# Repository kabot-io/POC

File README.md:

# Kabot - lowering entry barrier to ROS2

The Kabot robot is a hardware and software solution that lowers the entry barrier to Robot Operating System 2 (ROS2) and provides an expandable platform for makers, students and educators. One of the main obstacles in the adoption of ROS2 by beginners is the high knowledge barrier needed to setup and start tinkering - Kabot mission is to bring batteries included in a box. Think of using Arduino instead of setting up whole toolchain and build system.

The robot is a simple differential drive robot with expansion port for connecting external sensors and actuators, and instead of classic internal odometry sensors uses external camera to track itself in the world. Main goals are to create as simple (thus cost effective) hardware, move as much of heavy lifting as possible to the host PC instead of the robot itself and provide user with simple software environment.

## Hardware
All of the structural parts are designed for FDM printing. Wheels, base, cell holder - PLA will do. For the tires, standard O-Ring seals are used, as they are easily available for a cost next to nothing.

Kabot has two actuators - MG90S servos in a continous rotation version. This way, no on-board H-Bridge is needed, just one GPIO per motor and 5V power. Those servos also come with horns that can be used to attach wheels securely. 

All the electrons needed to keep the robot running are supplied via single 18650 Li-Ion cell. Charging, battery protection, and switching on and off is provided via IPS5306 - chinesium powerbank IC. Power for the charger is supplied via USB-C connector. This converter provides 5V for the servos and expansion port, and LDO provides 3.3V for the SoC and expansion port.

The main board is based around ESP32-S3 chip, sporting 16MB of flash and 8MB of RAM. Why ESP32-S3 instead of base ESP32? S3 has built-in USB peripheral, that hosts USB-JTAG and USB-CDC out of the box, so flashing, GDB and Serial.println() works without any external hardware. Furthermore, S3 is a little beefier, and has reconfigurable GPIO matrix, which will ease development of add-on boards. Most of the communication and other internal peripherals can be configured to use any pin of the package. 

## Installation

To run the robots, you need to install ROS2 Foxy. ROS2 is a software framework designed for robotic systems development. It provides a set of libraries and tools to help developers create robust and complex robot applications.

To install ROS2 Foxy, please follow the instructions provided on the official ROS2 website: [ROS2 Foxy installation](https://docs.ros.org/en/foxy/Installation.html)

## How to launch
To launch the package, you need to run the following command:
```
ros2 launch kabot_launcher kabot.launch.py
```

This will launch the package and start the necessary nodes and processes. If you encounter any issues while launching the package, please make sure to check whether you have all the required dependent packages. You can use the ROS2 package manager (rosdep) to automatically install all required dependencies.

## License

[Hardware: Creative Commons Attribution-NonCommercial-ShareAlike 4.0 International License](https://github.com/kabot-io/POC/blob/main/hardware/LICENSE)

[Software: Apache License, Version 2.0](https://github.com/kabot-io/POC/blob/main/src/LICENSE)

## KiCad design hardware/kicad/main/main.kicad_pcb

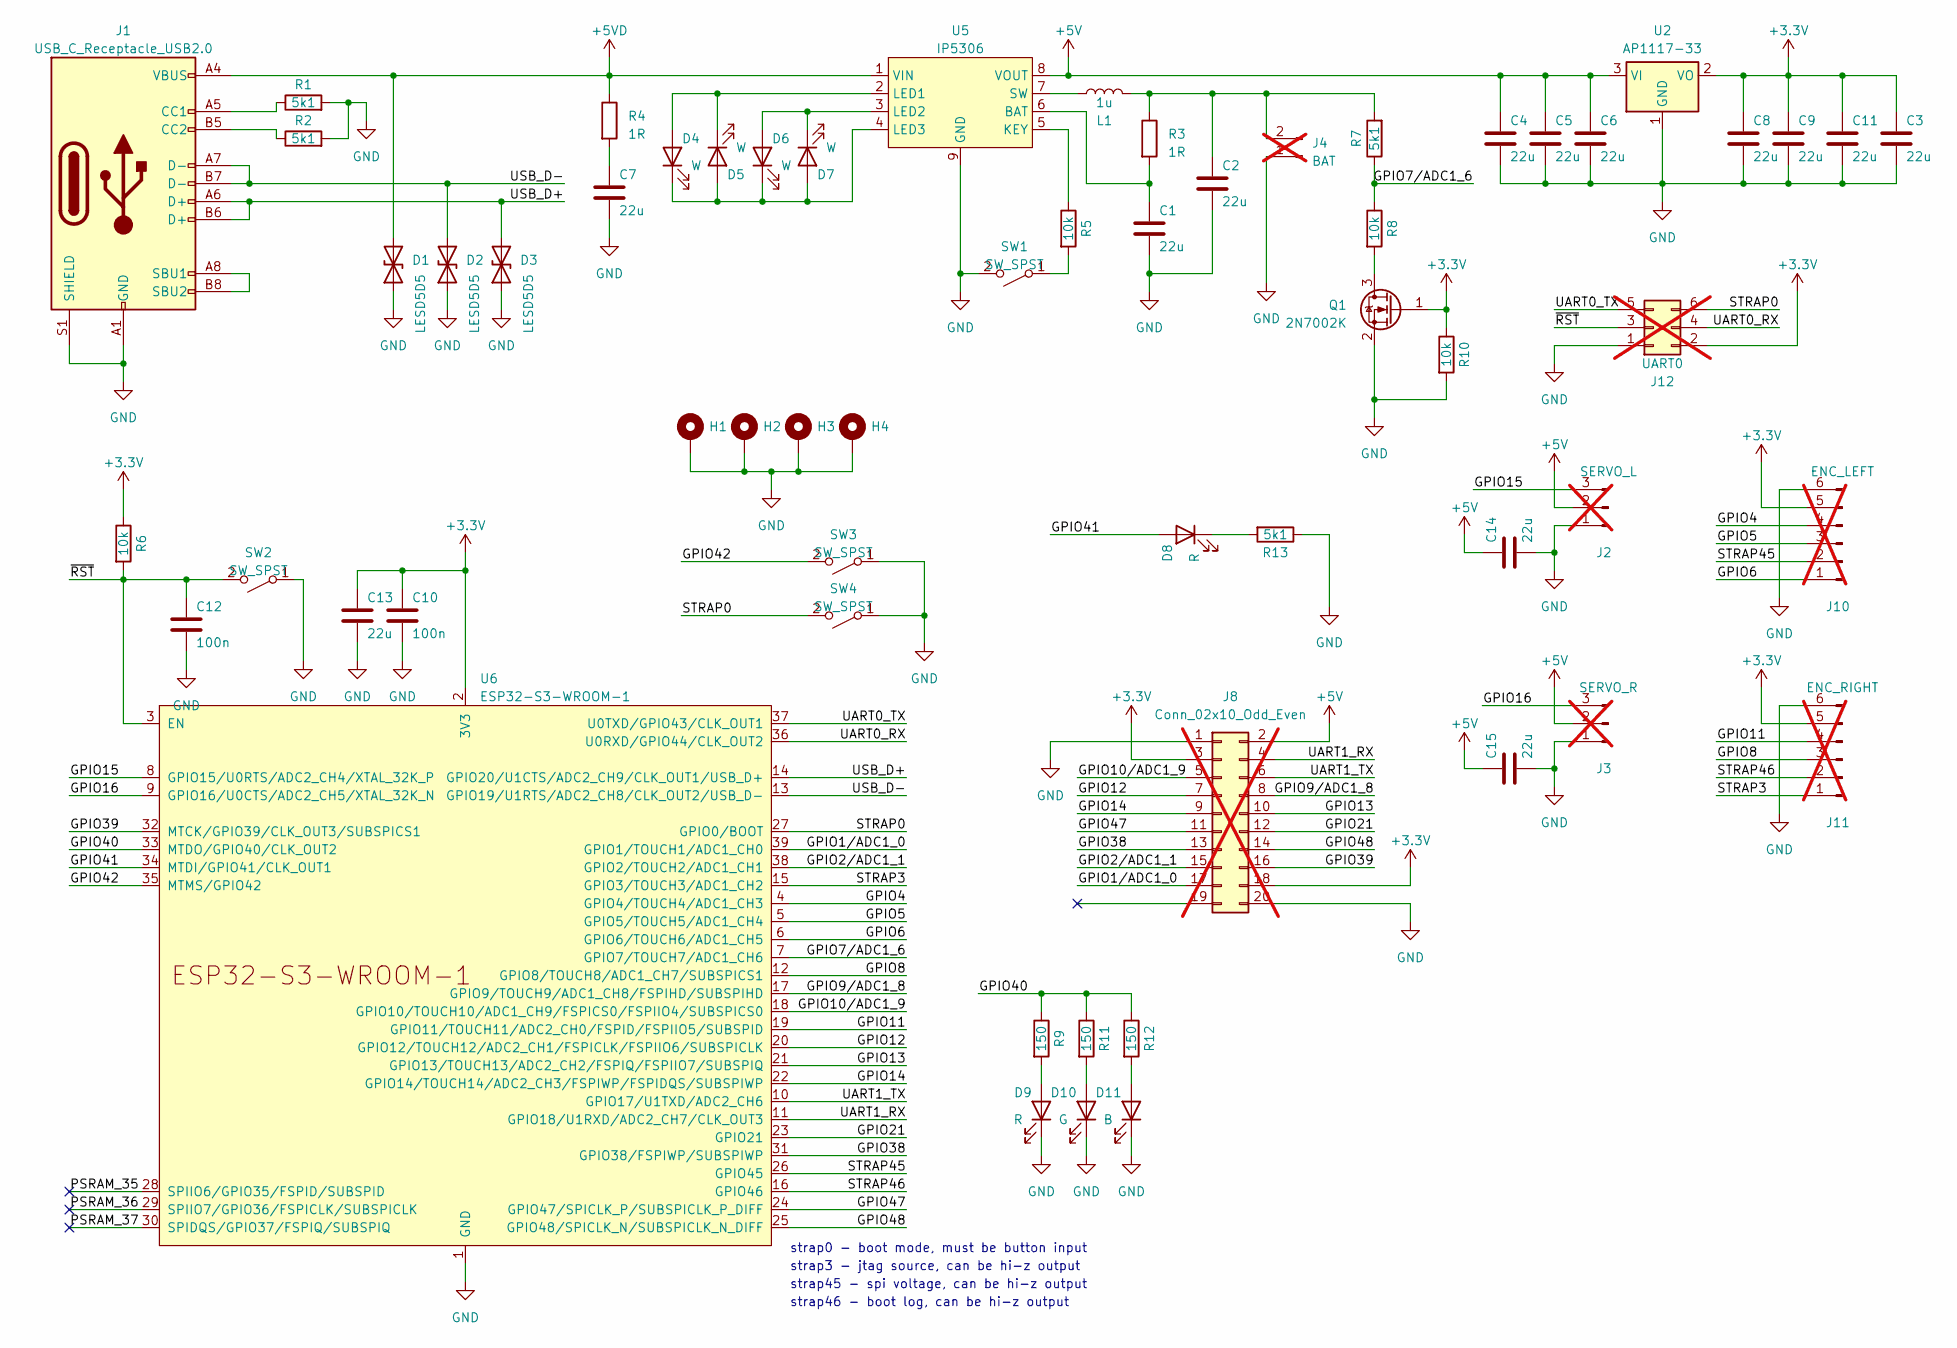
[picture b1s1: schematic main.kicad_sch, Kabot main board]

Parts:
C1, C2, C3, C4, C5, C6, C7, C8, C9, C11, C13, C14, C15: 22u; C_1206_3216Metric; JLC C12891
C10, C12: 100n; C_0603_1608Metric; JLC C14663
D1, D2, D3: LESD5D5; D_SOD-523; JLC C383211
D4, D5, D6, D7: W; LED_0603_1608Metric; JLC C2290
D8, D9: R; LED_0603_1608Metric; JLC C2286
D10: G; LED_0603_1608Metric; JLC C72043
D11: B; LED_0603_1608Metric; JLC C72041
H1, H2, H3, H4: MountingHole_Pad; MountingHole_3.2mm_M3_DIN965_Pad
J1: USB_C_Receptacle_USB2.0; USB_C_Receptacle_HRO_TYPE-C-31-M-12; JLC C668624
J2: SERVO_L; PinHeader_1x03_P2.54mm_Horizontal; not fitted
J3: SERVO_R; PinHeader_1x03_P2.54mm_Horizontal; not fitted
J4: BAT; PinHeader_1x02_P2.54mm_Horizontal; not fitted
J8: Conn_02x10_Odd_Even; PinSocket_2x10_P2.54mm_Vertical; JLC C124419; not fitted
J10: ENC_LEFT; PinHeader_1x06_P2.54mm_Horizontal; not fitted
J11: ENC_RIGHT; PinHeader_1x06_P2.54mm_Horizontal; not fitted
J12: UART0; PinHeader_2x03_P2.54mm_Vertical; not fitted
L1: 1u; L_Changjiang_FNR5045S; JLC C436396
Q1: 2N7002K; SOT-23; JLC C8545
R1, R2, R7, R13: 5k1; R_0603_1608Metric; JLC C23186
R3, R4: 1R; R_0603_1608Metric; JLC C22936
R5, R6, R8, R10: 10k; R_0603_1608Metric; JLC C25804
R9, R11, R12: 150; R_0603_1608Metric; JLC C22808
SW1, SW2, SW3, SW4: SW_SPST; SW_SPST_SKQG_WithStem; JLC C318884
U2: AP1117-33; SOT-223-3_TabPin2; JLC C6186
U5: IP5306; Diodes_SO-8EP; JLC C181692
U6: ESP32-S3-WROOM-1; JLC C2913202

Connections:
+3.3V: C3.1, C8.1, C9.1, C10.1, C11.1, C13.1, J8.3, J8.18, J10.5, J11.5, J12.2, Q1.1 (G), R6.1, R10.1, U2.2 (VO), U6.2 (3V3)
+5V: C4.1, C5.1, C6.1, C14.1, C15.1, J2.2, J3.2, J8.2, U2.3 (VI), U5.8 (VOUT)
+5VD: D1.2 (A2), J1.A4 (VBUS), J1.A9 (VBUS), J1.B4 (VBUS), J1.B9 (VBUS), R4.1, U5.1 (VIN)
/GPIO1/ADC1_0: J8.17, U6.39 (GPIO1/TOUCH1/ADC1_CH0)
/GPIO2/ADC1_1: J8.15, U6.38 (GPIO2/TOUCH2/ADC1_CH1)
/GPIO4: J10.4, U6.4 (GPIO4/TOUCH4/ADC1_CH3)
/GPIO5: J10.3, U6.5 (GPIO5/TOUCH5/ADC1_CH4)
/GPIO6: J10.1, U6.6 (GPIO6/TOUCH6/ADC1_CH5)
/GPIO7/ADC1_6: R7.1, R8.1, U6.7 (GPIO7/TOUCH7/ADC1_CH6)
/GPIO8: J11.3, U6.12 (GPIO8/TOUCH8/ADC1_CH7/SUBSPICS1)
/GPIO9/ADC1_8: J8.8, U6.17 (GPIO9/TOUCH9/ADC1_CH8/FSPIHD/SUBSPIHD)
/GPIO10/ADC1_9: J8.5, U6.18 (GPIO10/TOUCH10/ADC1_CH9/FSPICS0/FSPIIO4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)
/GPIO11: J11.4, U6.19 (GPIO11/TOUCH11/ADC2_CH0/FSPID/FSPIIO5/S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)
/GPIO12: J8.7, U6.20 (GPIO12/TOUCH12/ADC2_CH1/FSPICLK/FSPIIO6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)
/GPIO13: J8.10, U6.21 (GPIO13/TOUCH13/ADC2_CH2/FSPIQ/FSPIIO7/S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)
/GPIO14: J8.9, U6.22 (GPIO14/TOUCH14/ADC2_CH3/FSPIWP/FSPIDQS/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)
/GPIO15: J2.3, U6.8 (GPIO15/U0RTS/ADC2_CH4/XTAL_32K_P)
/GPIO16: J3.3, U6.9 (GPIO16/U0CTS/ADC2_CH5/XTAL_32K_N)
/GPIO21: J8.12, U6.23 (GPIO21)
/GPIO38: J8.13, U6.31 (GPIO38/FSPIWP/SUBSPIWP)
/GPIO39: J8.16, U6.32 (MTCK/GPIO39/CLK_OUT3/SUBSPICS1)
/GPIO40: R9.1, R11.1, R12.1, U6.33 (MTDO/GPIO40/CLK_OUT2)
/GPIO41: D8.2 (A), U6.34 (MTDI/GPIO41/CLK_OUT1)
/GPIO42: SW3.2 (B), U6.35 (MTMS/GPIO42)
/GPIO47: J8.11, U6.24 (GPIO47/SPICLK_P/SUBSPICLK_P_DIFF)
/GPIO48: J8.14, U6.25 (GPIO48/SPICLK_N/SUBSPICLK_N_DIFF)
/PSRAM_35: U6.28 (SPIIO6/GPIO35/FSPID/SUBSPID)
/PSRAM_36: U6.29 (SPIIO7/GPIO36/FSPICLK/SUBSPICLK)
/PSRAM_37: U6.30 (SPIDQS/GPIO37/FSPIQ/SUBSPIQ)
/STRAP0: J12.6, SW4.2 (B), U6.27 (GPIO0/BOOT)
/STRAP3: J11.1, U6.15 (GPIO3/TOUCH3/ADC1_CH2)
/STRAP45: J10.2, U6.26 (GPIO45)
/STRAP46: J11.2, U6.16 (GPIO46)
/UART0_RX: J12.4, U6.36 (U0RXD/GPIO44/CLK_OUT2)
/UART0_TX: J12.5, U6.37 (U0TXD/GPIO43/CLK_OUT1)
/UART1_RX: J8.4, U6.11 (GPIO18/U1RXD/ADC2_CH7/CLK_OUT3)
/UART1_TX: J8.6, U6.10 (GPIO17/U1TXD/ADC2_CH6)
/USB_D+: D3.2 (A2), J1.A6 (D+), J1.B6 (D+), U6.14 (GPIO20/U1CTS/ADC2_CH9/CLK_OUT1/USB_D+)
/USB_D-: D2.2 (A2), J1.A7 (D-), J1.B7 (D-), U6.13 (GPIO19/U1RTS/ADC2_CH8/CLK_OUT2/USB_D-)
/~RST: C12.1, J12.3, R6.2, SW2.2 (B), U6.3 (EN)
GND: C1.2, C2.2, C3.2, C4.2, C5.2, C6.2, C7.2, C8.2, C9.2, C10.2, C11.2, C12.2, C13.2, C14.2, C15.2, D1.1 (A1), D2.1 (A1), D3.1 (A1), D9.1 (K), D10.1 (K), D11.1 (K), H1.1, H2.1, H3.1, H4.1, J1.A1 (GND), J1.A12 (GND), J1.B1 (GND), J1.B12 (GND), J1.S1 (SHIELD), J2.1, J3.1, J4.1, J8.1, J8.20, J10.6, J11.6, J12.1, Q1.2 (S), R1.2, R2.2, R10.2, R13.1, SW1.2 (B), SW2.1 (A), SW3.1 (A), SW4.1 (A), U2.1 (GND), U5.9 (GND), U6.1 (GND), U6.40 (GND), U6.41 (GND)
unnamed: C7.1, R4.2
unnamed: D4.2 (A), D5.1 (K), U5.2 (LED1)
unnamed: D4.1 (K), D5.2 (A), D6.1 (K), D7.2 (A), U5.4 (LED3)
unnamed: D6.2 (A), D7.1 (K), U5.3 (LED2)
unnamed: D8.1 (K), R13.2
unnamed: D9.2 (A), R9.2
unnamed: D10.2 (A), R11.2
unnamed: D11.2 (A), R12.2
unnamed: J1.A5 (CC1), R1.1
unnamed: J1.B5 (CC2), R2.1
unnamed: J1.A8 (SBU1), J1.B8 (SBU2)
unnamed: C2.1, J4.2, L1.2, R3.1, R7.2
unnamed: Q1.3 (D), R8.2
unnamed: R5.2, SW1.1 (A)
unnamed: C1.1, R3.2, U5.6 (BAT)
unnamed: R5.1, U5.5 (KEY)
unnamed: L1.1, U5.7 (SW)

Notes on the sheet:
strap3 - jtag source, can be hi-z output
strap45 - spi voltage, can be hi-z output
strap0 - boot mode, must be button input
strap46 - boot log, can be hi-z output

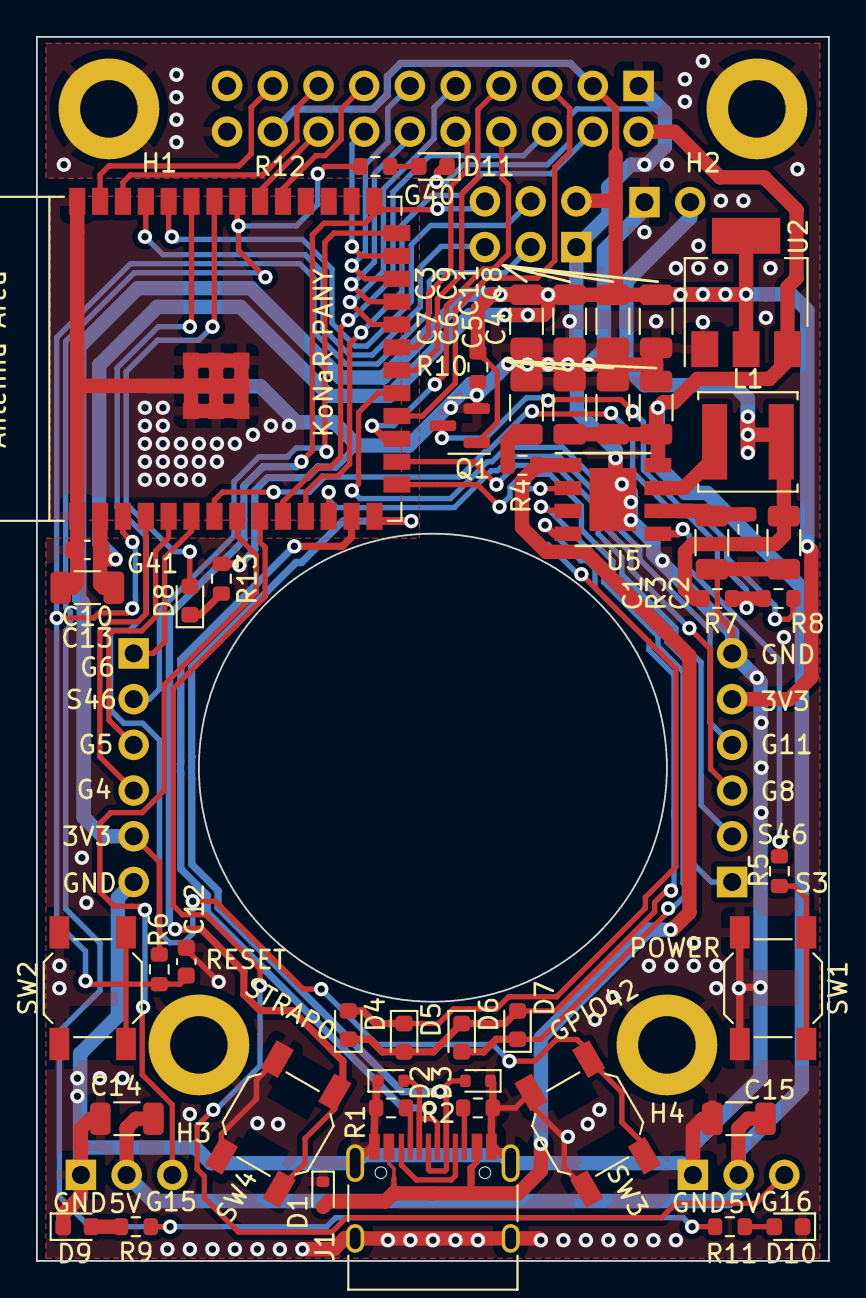
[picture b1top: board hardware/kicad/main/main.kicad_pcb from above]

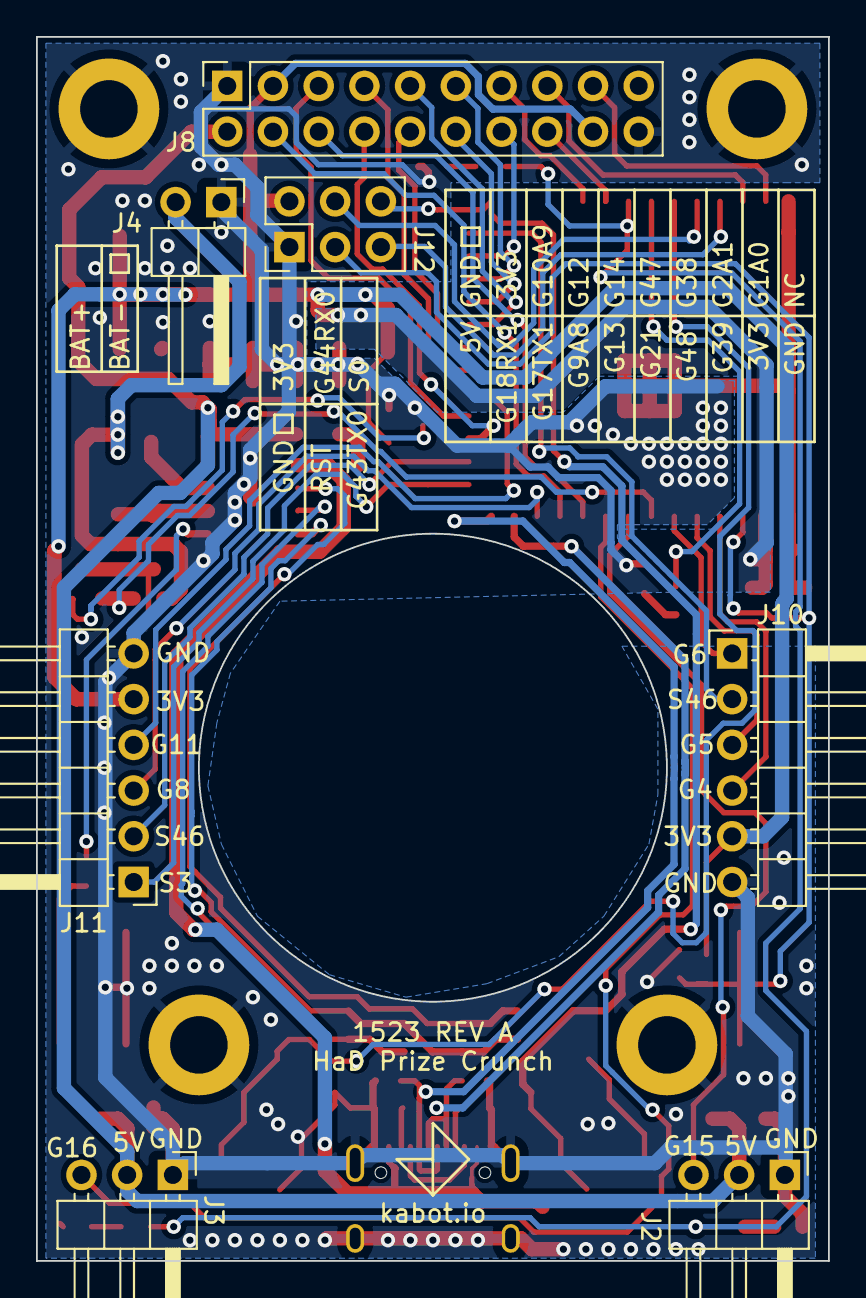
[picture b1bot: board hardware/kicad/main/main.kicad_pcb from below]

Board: 2 copper layers, 44.0 x 68.0 mm, 60 parts (7 on the bottom side), 55 nets.

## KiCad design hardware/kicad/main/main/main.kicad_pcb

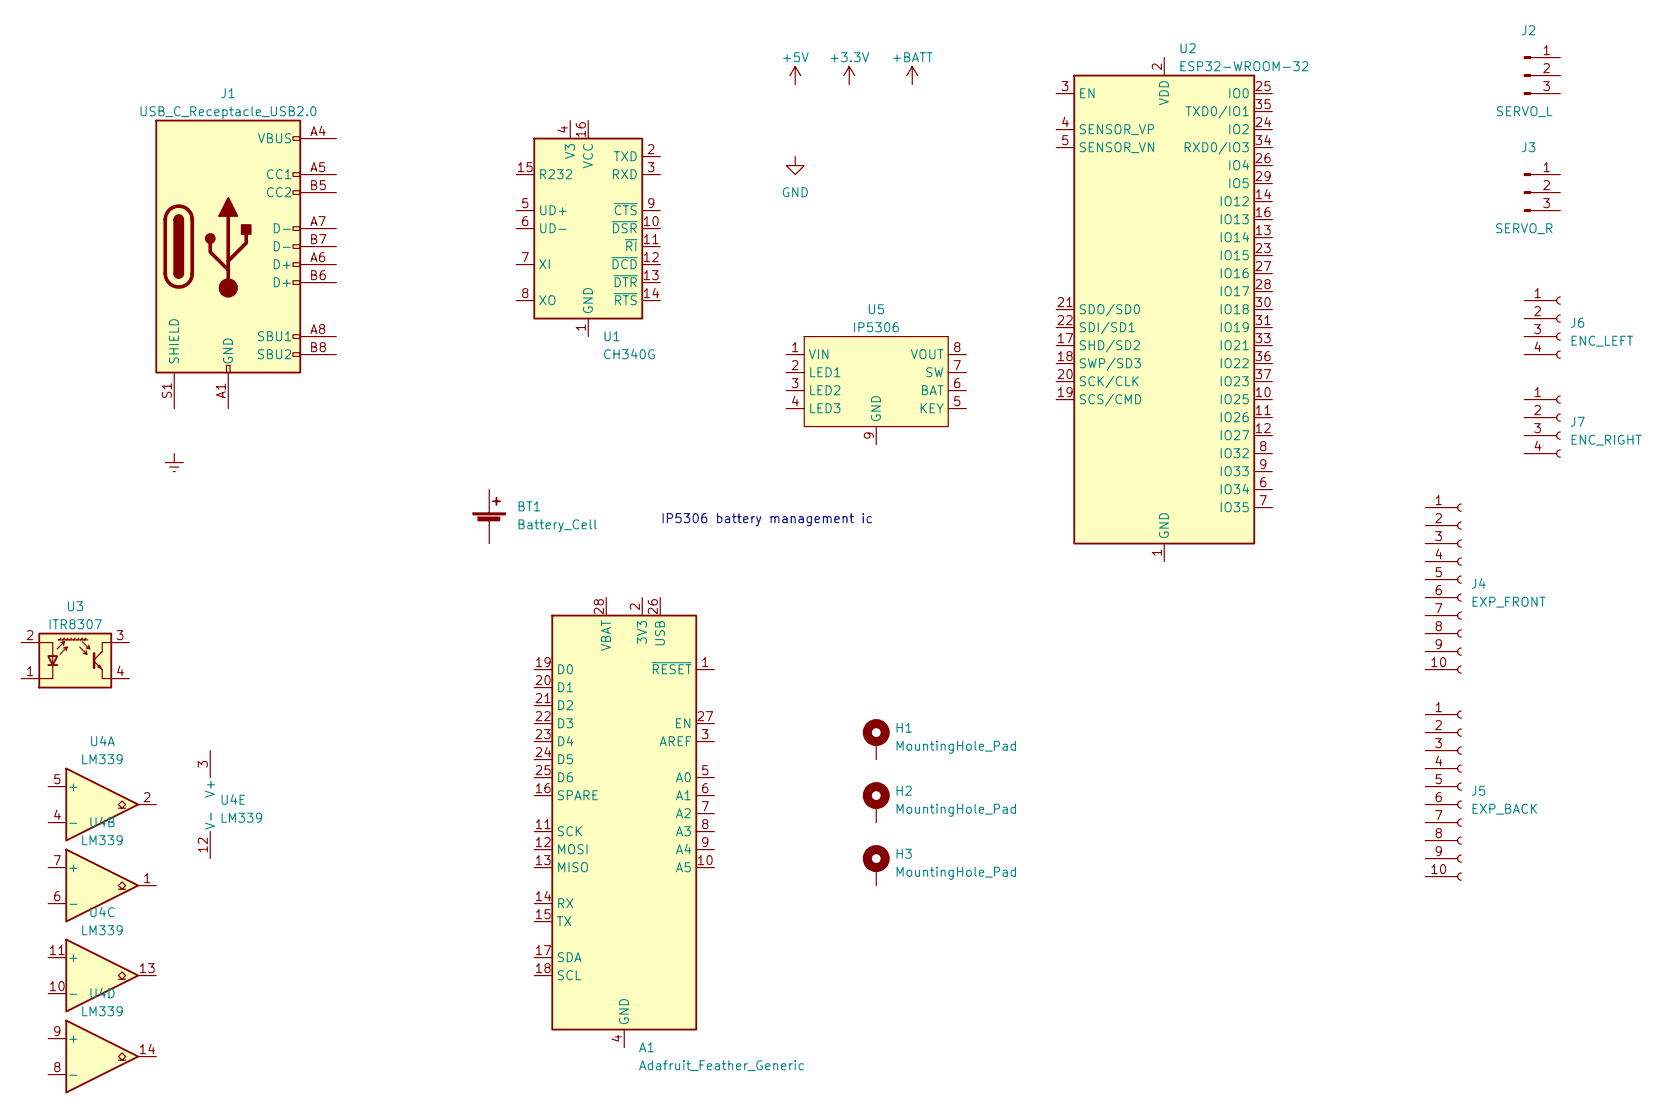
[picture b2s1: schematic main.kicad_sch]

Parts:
A1: Adafruit_Feather_Generic; Adafruit_Feather
BT1: Battery_Cell; BatteryHolder_MPD_BH-18650-PC2
H1, H2, H3: MountingHole_Pad; MountingHole_3.2mm_M3_DIN965_Pad
J1: USB_C_Receptacle_USB2.0; USB_C_Receptacle_HRO_TYPE-C-31-M-12
J2: SERVO_L; PinHeader_1x03_P2.54mm_Horizontal
J3: SERVO_R; PinHeader_1x03_P2.54mm_Horizontal
J4: EXP_FRONT; PinSocket_1x10_P2.54mm_Horizontal
J5: EXP_BACK; PinSocket_1x10_P2.54mm_Horizontal
J6: ENC_LEFT; PinSocket_1x04_P2.54mm_Horizontal
J7: ENC_RIGHT; PinSocket_1x04_P2.54mm_Horizontal
U1: CH340G; SOIC-16_3.9x9.9mm_P1.27mm
U2: ESP32-WROOM-32
U3: ITR8307; Everlight_ITR8307
U4: LM339; SOIC-14_3.9x8.7mm_P1.27mm
U5: IP5306; Diodes_SO-8EP

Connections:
unnamed: J1.A1 (GND), J1.A12 (GND), J1.B1 (GND), J1.B12 (GND)
unnamed: J1.A4 (VBUS), J1.A9 (VBUS), J1.B4 (VBUS), J1.B9 (VBUS)
unnamed: U2.1 (GND), U2.15 (GND), U2.38 (GND), U2.39 (GND)

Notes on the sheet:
IP5306 battery management ic

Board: 2 copper layers, 17 parts (1 on the bottom side), 3 nets, no tracks yet.

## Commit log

2023-02-28 Initial commit. Launcher for app and uros agent
2023-03-01 KabotServo struct
2023-03-08 initial hardware dump
2023-03-09 added battery charging ic, mounting holes
2023-03-09 fixed paths to be relative, added kicad gitignore, removed auto backups
2023-03-09 added model of wheel
2023-03-10 added espressif libraries as submodule
2023-03-10 used espressif library
2023-03-10 fixed paths
2023-03-20 Aruco submodule
2023-03-22 Aruco detection. Usb camera config files. Improved kabot.launch
2023-03-22 Camera config files, default rviz2 launch
2023-04-11 Updated aruco exmaple
2023-04-11 Updated launcher
2023-04-11 URDF, improved launcher script
2023-04-12 most of the routing done, left power supplies and navigation leds
2023-04-12 Added inertial macros for wheels and chassis
2023-04-12 routing pretty much done, passing DRC
2023-04-13 Gazebo diff_drive_controller
2023-04-14 changed buttons to basic ones, fixed inductor footprint, added JLCPCB part numbers to each mounted component for assembly
2023-04-14 minor dimensions adjustments
2023-04-14 removed addressable led as it is not really available, fixed inductor footprint, added production files
2023-04-17 fixed inductor model, added some drawings and dimensions
2023-04-17 added blend files and stl of chassis
2023-04-18 added interactive bom, updated blend files with more clearance on 18650 cell
2023-04-18 moved bom to docs to enable github pages
2023-04-24 added licenses; Apache 2 for code, CC NC-BY-SA for hardware
2023-04-24 First small readme, additional launch files
2023-04-25 Improved readme.md: how to launch kabot
2023-04-25 Updated licenses links, added kabot photo to readme.md
2023-04-25 Updated readme header image
2023-04-25 Updated licenses
2023-04-26 Spawning multiple robots in gazebo sim
2023-04-26 Git submodules clean
